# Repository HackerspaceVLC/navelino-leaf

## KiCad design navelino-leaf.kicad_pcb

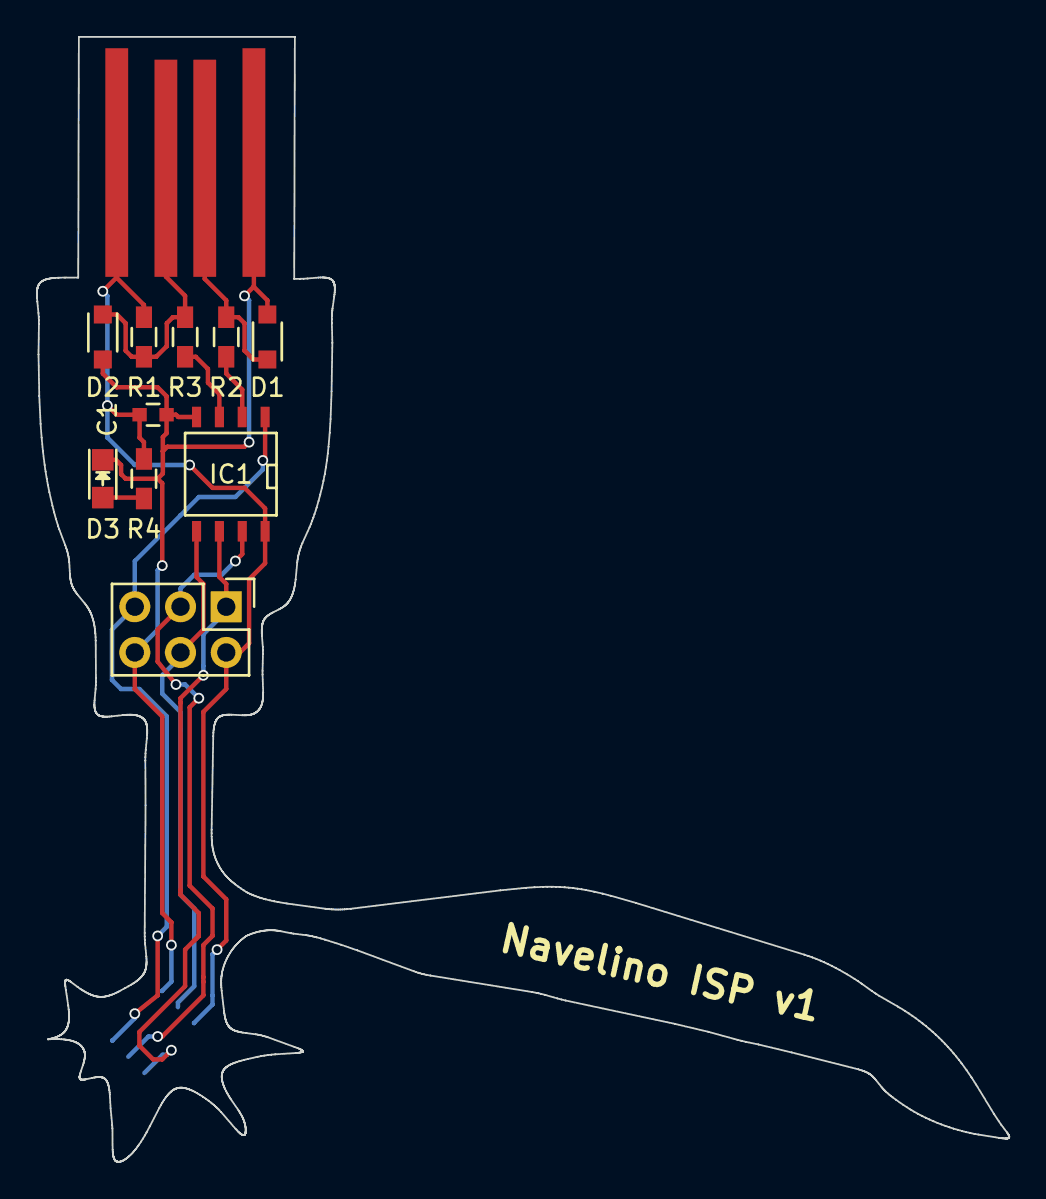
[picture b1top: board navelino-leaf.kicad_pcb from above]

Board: 2 copper layers, 54.0 x 62.5 mm, 12 parts (1 on the bottom side), 11 nets.

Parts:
C1: 0.1uF; C_0603
D1: ZENNER 3V6; SOD-323_HandSoldering
D2: ZENER 3V6; SOD-323_HandSoldering
D3: LED; LED_0805
IC1: ATTINY45-S; SOIC-8-N
ISP: CONN_02X03; ISPSMD
P2: CONN_01X04; USB-A-PCB
P3: CONN_02X03; Pin_Header_Straight_2x03
R1: 1.5K; R_0603_HandSoldering
R2, R3: 68; R_0603_HandSoldering
R4: 330; R_0603_HandSoldering

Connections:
D+: D1.1, P2.3, R2.1
D-: D2.1, P2.2, R1.2, R3.1
GND: C1.2, D1.2, D2.2, D3.1, IC1.4, ISP.6, P2.4, P3.6
MISO: IC1.6, ISP.1, P3.1
MOSI: IC1.5, ISP.4, P3.4
unnamed: D3.2, R4.2
unnamed: IC1.2, R2.2
unnamed: IC1.3, R3.2
RESET: IC1.1, ISP.5, P3.5
SCK: IC1.7, ISP.3, P3.3
VCC: C1.1, IC1.8, ISP.2, P2.1, P3.2, R1.1, R4.1

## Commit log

2016-11-23 Import inicial V1
2016-11-23 Corregido footprint del SOIC8 Re-enrutado de ISP SMD Un poco de amor al Silkscreen de los diodos
